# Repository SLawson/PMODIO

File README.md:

## PMODIO

#### Project Description
The PMODIO device is an IO expansion for use with the Digilent Nexys4DDR board. It has a 128x64 dot-matrix graphical display and a quadrature rotary encoder. It connects to to Nexys4DDR's expansion headers (JA & JB by default, but this can be configured).

This project contains a CadSoft EAGLE schematic and board layout, and bill of materials for constructing them from scratch. It also contains a Xilinx custom peripheral IP with drivers for interfacing with the board.

#### Repository Layout

	/doc
    	/datasheets						Third-party datasheets for all BOM components
        BOM.xlsx						Bill of materials
        PMODIO_DriverReference.pdf		PMODIO driver reference
        PMODIO_UserGuide.pdf			User guide for hardware and the peripheral
    /src
    	/doc							Documentation source files
        /function_test					Source code for a Vivado and Xilinx SDK project 
        								to verify breadboard/PCB functionality
                                        	- also provides driver usage examples
        /physical						Eagle schematic and board layout, solder stencil
        /PMODIO_1.0						Peripheral IP block
    /LICENSE							License description (GPL v3)
        
#### Repository Branches
 
| Branch Name 	|	Purpose 												|
|---------------|-----------------------------------------------------------|
| master	  	| release branch 											|
| rev1			| latest development for board revision 1.x					|
| dev			| development - will always correspond to latest board rev	|

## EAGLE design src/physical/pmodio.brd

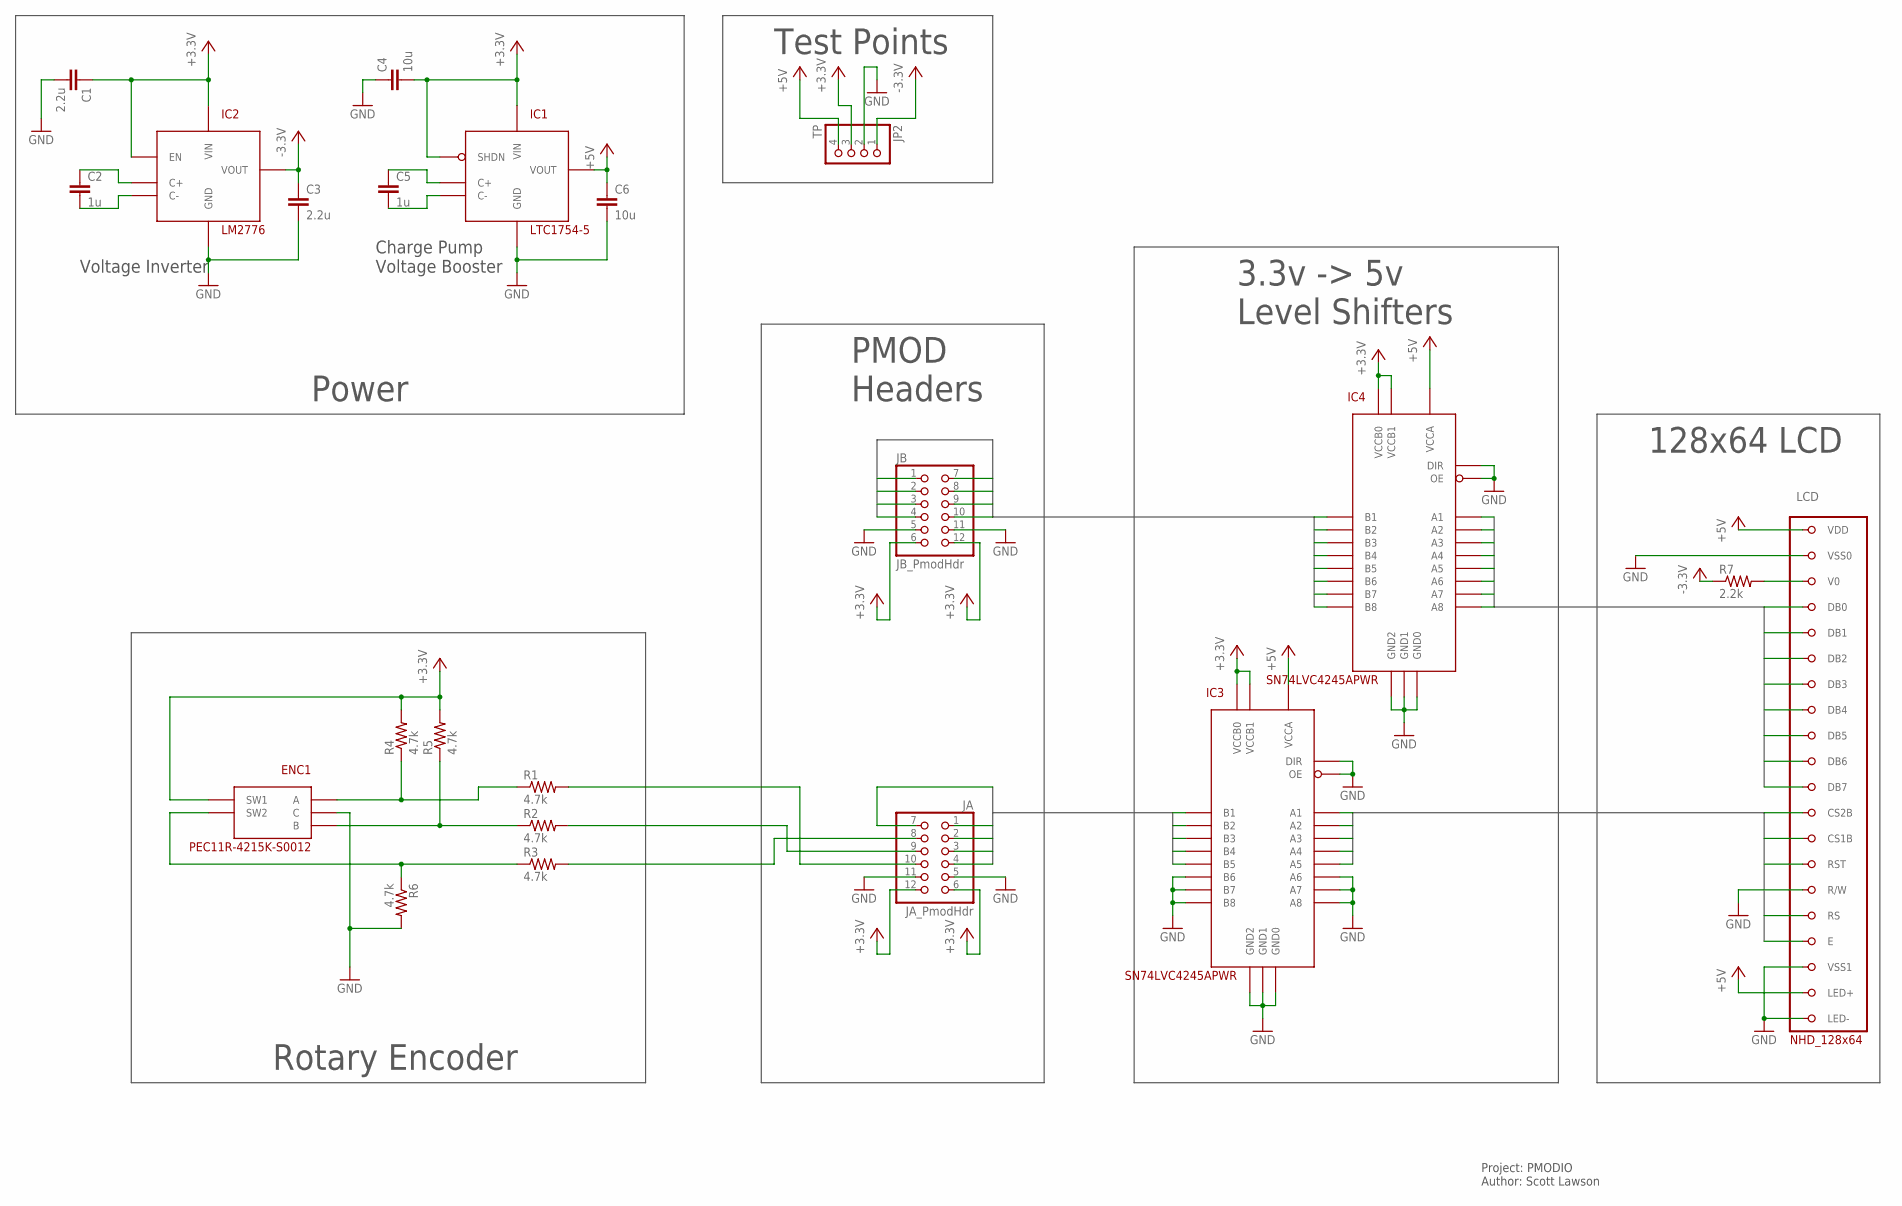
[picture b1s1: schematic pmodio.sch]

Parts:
C1, C3: 2.2u; C0402
C2, C5: 1u; C0402
C4, C6: 10u; C0805
ENC1: PEC11R-4215K-S0012; PEC11R-4XXXF-SXXXX
IC1: LTC1754-5; SOT23-6
IC2: LM2776; SOT23-6
IC3, IC4: SN74LVC4245APWR; TSSOP24
JA: JA_PmodHdr; 2X06/90
JB: JB_PmodHdr; 2X06/90
JP2: TP; 1X04
LCD: NHD_128x64; NHD-12864MZ-FSW-GBW-L
R1, R2, R3, R4, R5, R6: 4.7k; R0603
R7: 2.2k; R0603

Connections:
+3.3V: C1.1, C4.2, ENC1.SW1, IC1.3 (SHDN), IC1.5 (VIN), IC2.3 (VIN), IC2.4 (EN), IC3.23 (VCCB0), IC3.24 (VCCB1), IC4.23 (VCCB0), IC4.24 (VCCB1), JA.6, JA.12, JB.6, JB.12, JP2.3, R4.2, R5.2
+5V: C6.1, IC1.1 (VOUT), IC3.1 (VCCA), IC4.1 (VCCA), JP2.4, LCD.LED+, LCD.VDD
-3.3V: C3.1, IC2.1 (VOUT), JP2.1, R7.1
CNTLB_3.3V0: IC3.21 (B1), JA.4
CNTLB_3.3V1: IC3.20 (B2), JA.3
CNTLB_3.3V2: IC3.19 (B3), JA.2
CNTLB_3.3V3: IC3.18 (B4), JA.7
CNTLB_3.3V4: IC3.17 (B5), JA.1
CNTLB_5V0: IC3.3 (A1), LCD.CS2B
CNTLB_5V1: IC3.4 (A2), LCD.CS1B
CNTLB_5V2: IC3.5 (A3), LCD.RST
CNTLB_5V3: IC3.6 (A4), LCD.RS
CNTLB_5V4: IC3.7 (A5), LCD.E
DB_3.3V0: IC4.21 (B1), JB.10
DB_3.3V1: IC4.20 (B2), JB.4
DB_3.3V2: IC4.19 (B3), JB.9
DB_3.3V3: IC4.18 (B4), JB.3
DB_3.3V4: IC4.17 (B5), JB.8
DB_3.3V5: IC4.16 (B6), JB.2
DB_3.3V6: IC4.15 (B7), JB.7
DB_3.3V7: IC4.14 (B8), JB.1
DB_5V0: IC4.3 (A1), LCD.DB0
DB_5V1: IC4.4 (A2), LCD.DB1
DB_5V2: IC4.5 (A3), LCD.DB2
DB_5V3: IC4.6 (A4), LCD.DB3
DB_5V4: IC4.7 (A5), LCD.DB4
DB_5V5: IC4.8 (A6), LCD.DB5
DB_5V6: IC4.9 (A7), LCD.DB6
DB_5V7: IC4.10 (A8), LCD.DB7
GND: C1.2, C3.2, C4.1, C6.2, ENC1.C, IC1.2 (GND), IC2.2 (GND), IC3.2 (DIR), IC3.8 (A6), IC3.9 (A7), IC3.10 (A8), IC3.11 (GND0), IC3.12 (GND1), IC3.13 (GND2), IC3.14 (B8), IC3.15 (B7), IC3.16 (B6), IC3.22 (OE), IC4.2 (DIR), IC4.11 (GND0), IC4.12 (GND1), IC4.13 (GND2), IC4.22 (OE), JA.5, JA.11, JB.5, JB.11, JP2.2, LCD.LED-, LCD.RW (R/W), LCD.VSS0, LCD.VSS1, R6.2
unnamed: LCD.V0, R7.2
unnamed: C2.1, IC2.5 (C+)
unnamed: C2.2, IC2.6 (C-)
unnamed: C5.1, IC1.6 (C+)
unnamed: C5.2, IC1.4 (C-)
unnamed: ENC1.A, R1.1, R4.1
unnamed: ENC1.B, R2.1, R5.1
unnamed: ENC1.SW2, R3.1, R6.1
unnamed: JA.10, R1.2
unnamed: JA.8, R3.2
unnamed: JA.9, R2.2

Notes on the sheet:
Project: PMODIO Author: Scott Lawson
Voltage Inverter
Charge Pump Voltage Booster
Power
128x64 LCD
3.3v -> 5v Level Shifters
PMOD Headers
Rotary Encoder
Test Points

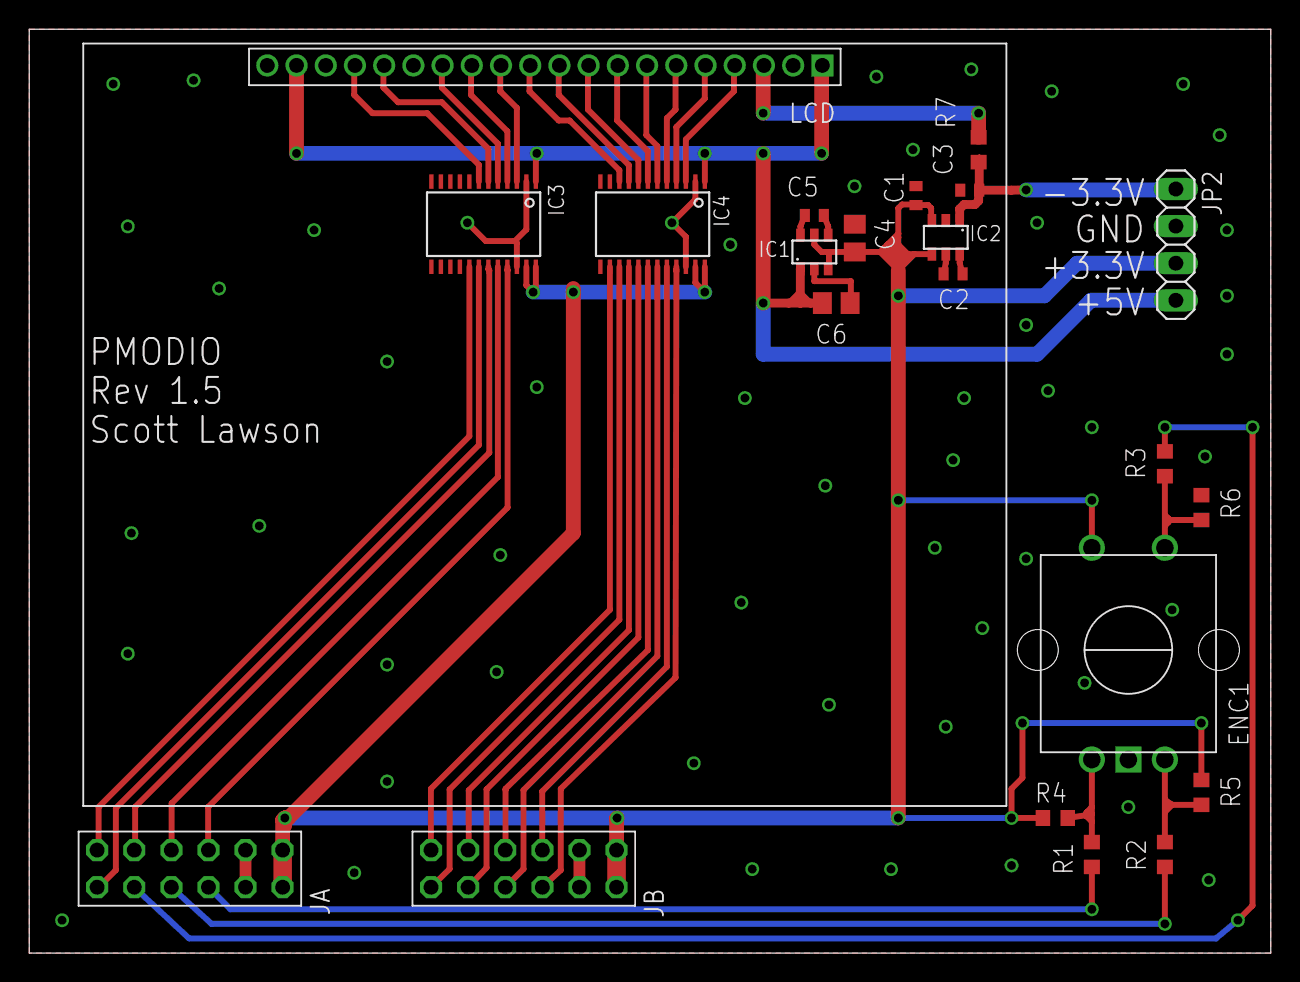
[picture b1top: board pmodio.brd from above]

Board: 2 copper layers, 85.0 x 63.2 mm, 22 parts (0 on the bottom side), 41 nets.

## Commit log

2016-03-19 .gitignore: added Vim swap files (*.swp)
2016-03-19 README.md: Initial version
2016-03-19 doc/: Initial push of documentation
2016-03-19 src/doc/: Initial push of documentation sources
2016-03-19 src/physical: Initial push of board sources
2016-03-19 .gitignore: Added non-Vim editor lock files
2016-03-19 README.md: Fixed whitespace typo
2016-03-19 src/function_test/: Initial push of function test sources
2016-03-19 src/PMODIO_1.0/: Initial push of PMODIO IP block
